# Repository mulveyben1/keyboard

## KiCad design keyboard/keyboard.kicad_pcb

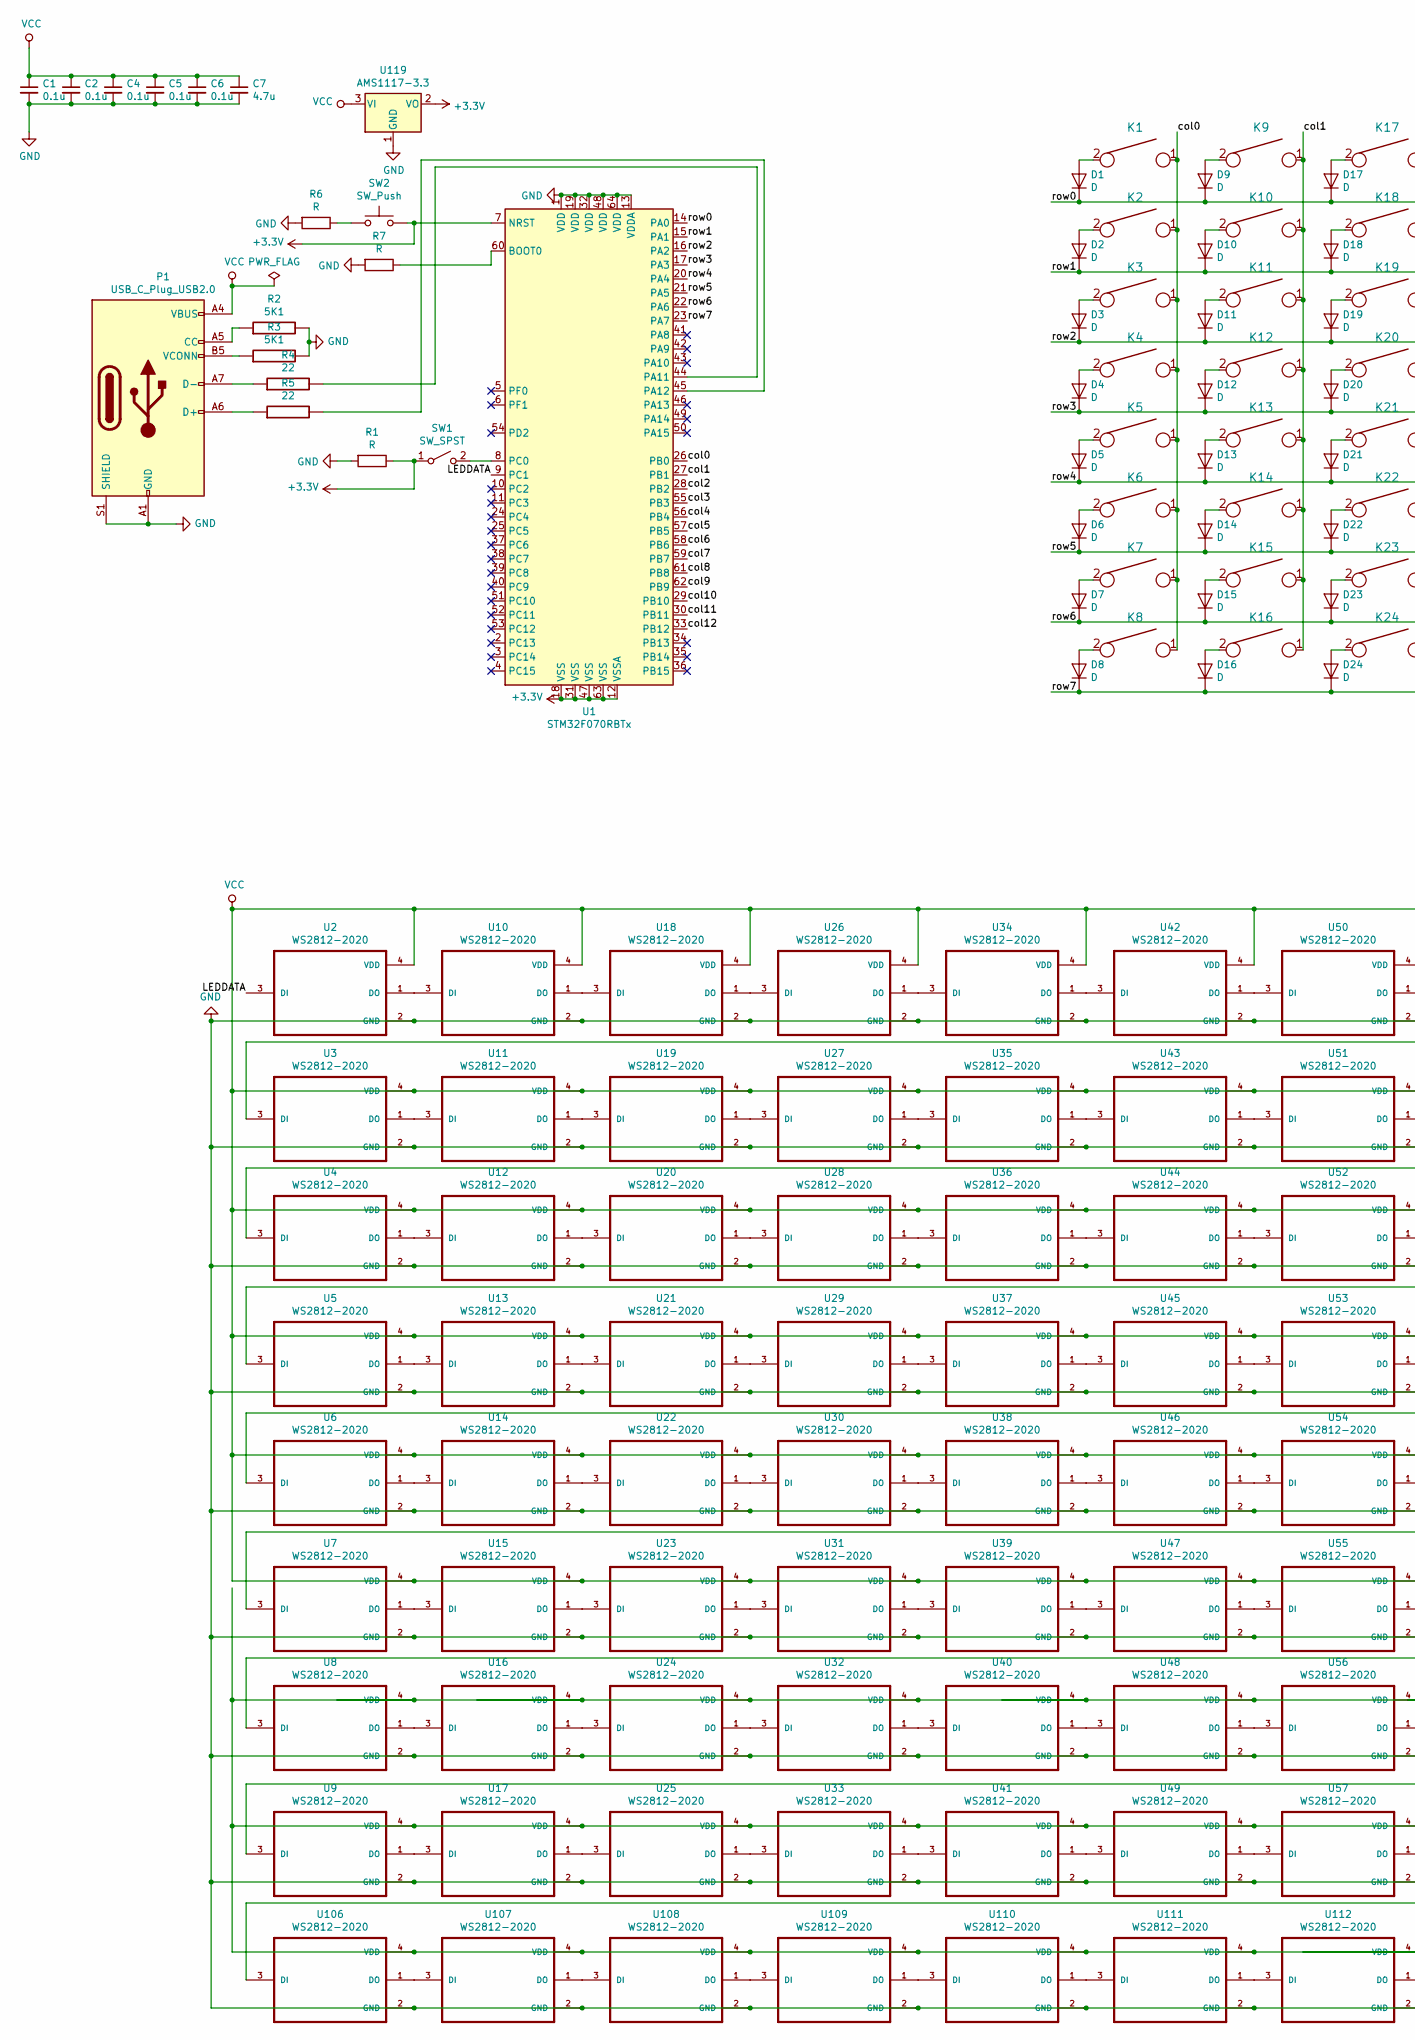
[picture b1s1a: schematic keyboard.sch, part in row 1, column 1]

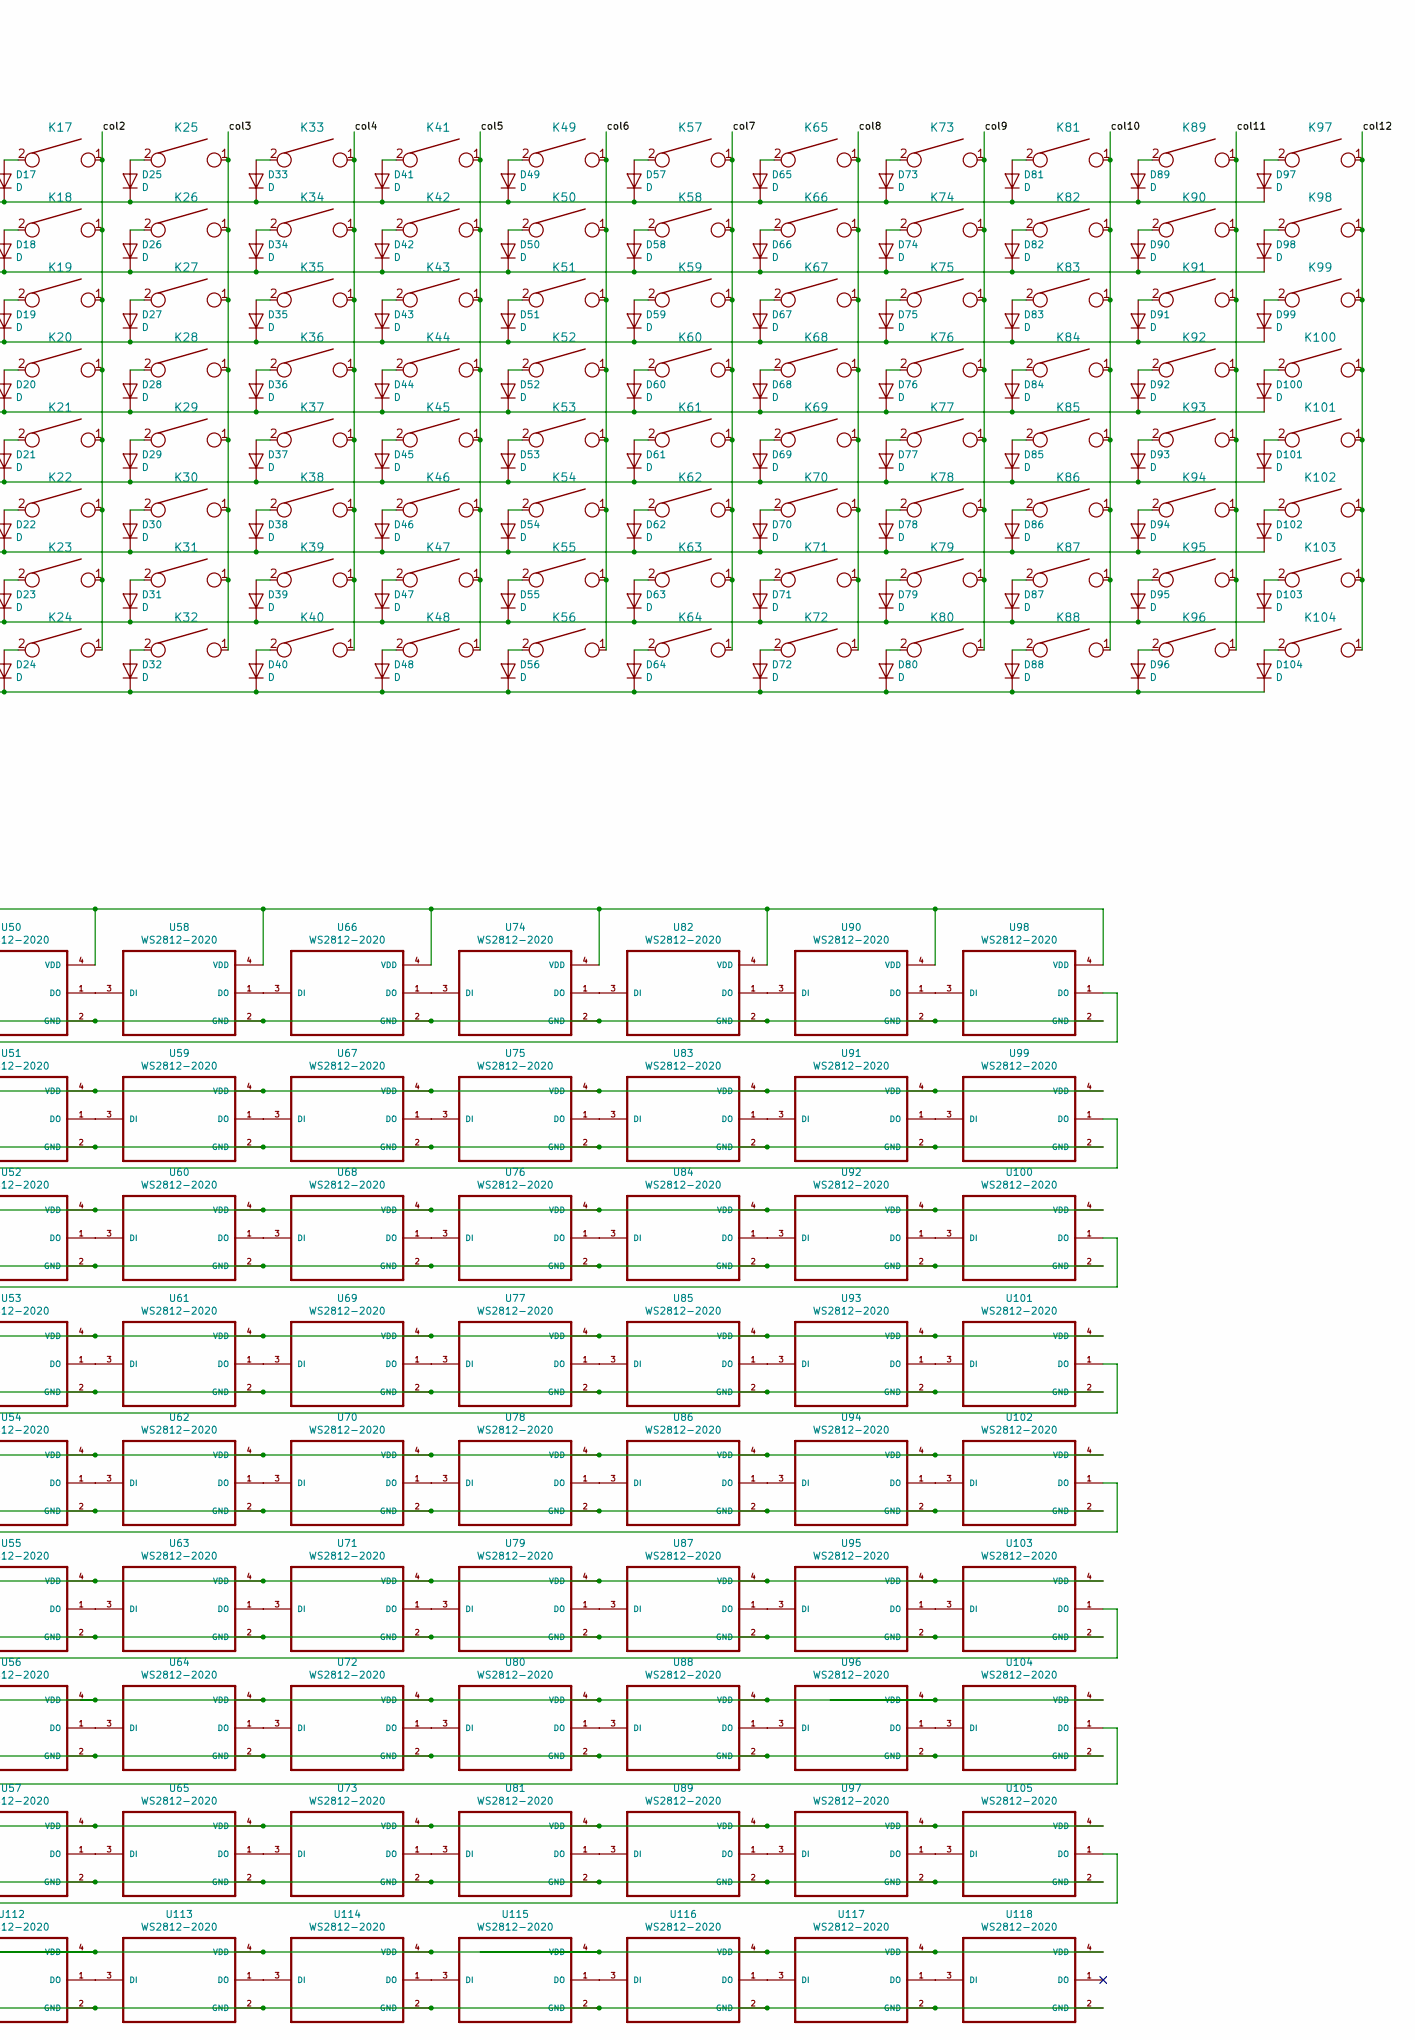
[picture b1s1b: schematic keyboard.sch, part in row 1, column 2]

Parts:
C1, C2, C4, C5, C6: 0.1u; C_0805_2012Metric
C7: 4.7u; C_0805_2012Metric
D1, D2, D3, D4, D5, D6, D7, D8, D9, D10, D11, D12, D13, D14, D15, D16, D17, D18, D19, D20, D21, D22, D23, D24, D25, D26, D27, D28, D29, D30, D31, D32, D33, D34, D35, D36, D37, D38, D39, D40, D41, D42, D43, D44, D45, D46, D47, D48, D49, D50, D51, D52, D53, D54, D55, D56, D57, D58, D59, D60, D61, D62, D63, D64, D65, D66, D67, D68, D69, D70, D71, D72, D73, D74, D75, D76, D77, D78, D79, D80, D81, D82, D83, D84, D85, D86, D87, D88, D89, D90, D91, D92, D93, D94, D95, D96, D97, D98, D99, D100, D101, D102, D103, D104: D; D_SOD123_axial
K1, K2, K3, K4, K5, K6, K7, K8, K9, K10, K11, K12, K13, K14, K15, K16, K17, K18, K19, K20, K21, K22, K23, K24, K25, K26, K27, K28, K29, K30, K31, K32, K33, K34, K35, K36, K37, K38, K39, K40, K41, K42, K43, K44, K45, K46, K47, K48, K49, K50, K51, K52, K53, K54, K55, K56, K57, K58, K59, K60, K61, K62, K63, K64, K65, K66, K67, K68, K69, K70, K71, K72, K73, K74, K75, K76, K77, K78, K79, K80, K81, K82, K83, K84, K85, K86, K87, K88, K89, K90, K91, K92, K93, K94, K95, K96, K97, K98, K99, K100, K101, K102, K103, K104: KEYSW; Mx_Alps_100
P1: USB_C_Plug_USB2.0; USB_C_Receptacle_Amphenol_12401548E4-2A
R1, R6, R7: R; C_0805_2012Metric
R2, R3: 5K1; R_0805_2012Metric
R4, R5: 22; R_0805_2012Metric
SW1: SW_SPST; SW_Slide_1P2T_CK_OS102011MS2Q
SW2: SW_Push; Push_E-Switch_KS01Q01
U1: STM32F070RBTx; LQFP-64_10x10mm_P0.5mm
U2, U3, U4, U5, U6, U7, U8, U9, U10, U11, U12, U13, U14, U15, U16, U17, U18, U19, U20, U21, U22, U23, U24, U25, U26, U27, U28, U29, U30, U31, U32, U33, U34, U35, U36, U37, U38, U39, U40, U41, U42, U43, U44, U45, U46, U47, U48, U49, U50, U51, U52, U53, U54, U55, U56, U57, U58, U59, U60, U61, U62, U63, U64, U65, U66, U67, U68, U69, U70, U71, U72, U73, U74, U75, U76, U77, U78, U79, U80, U81, U82, U83, U84, U85, U86, U87, U88, U89, U90, U91, U92, U93, U94, U95, U96, U97, U98, U99, U100, U101, U102, U103, U104, U105, U106, U107, U108, U109, U110, U111, U112, U113, U114, U115, U116, U117, U118: WS2812-2020; LED_WS2812-2020
U119: AMS1117-3.3; SOT-223-3_TabPin2

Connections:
+3V3: R1.1, SW1.1 (A), SW2.2, U1.7 (NRST), U1.12 (VSSA), U1.18 (VSS), U1.31 (VSS), U1.47 (VSS), U1.63 (VSS), U119.2 (VO)
/LEDDATA: U1.9 (PC1), U2.3 (DI)
/col0: K1.1, K2.1, K3.1, K4.1, K5.1, K6.1, K7.1, K8.1, U1.26 (PB0)
/col1: K9.1, K10.1, K11.1, K12.1, K13.1, K14.1, K15.1, K16.1, U1.27 (PB1)
/col2: K17.1, K18.1, K19.1, K20.1, K21.1, K22.1, K23.1, K24.1, U1.28 (PB2)
/col3: K25.1, K26.1, K27.1, K28.1, K29.1, K30.1, K31.1, K32.1, U1.55 (PB3)
/col4: K33.1, K34.1, K35.1, K36.1, K37.1, K38.1, K39.1, K40.1, U1.56 (PB4)
/col5: K41.1, K42.1, K43.1, K44.1, K45.1, K46.1, K47.1, K48.1, U1.57 (PB5)
/col6: K49.1, K50.1, K51.1, K52.1, K53.1, K54.1, K55.1, K56.1, U1.58 (PB6)
/col7: K57.1, K58.1, K59.1, K60.1, K61.1, K62.1, K63.1, K64.1, U1.59 (PB7)
/col8: K65.1, K66.1, K67.1, K68.1, K69.1, K70.1, K71.1, K72.1, U1.61 (PB8)
/col9: K73.1, K74.1, K75.1, K76.1, K77.1, K78.1, K79.1, K80.1, U1.62 (PB9)
/col10: K81.1, K82.1, K83.1, K84.1, K85.1, K86.1, K87.1, K88.1, U1.29 (PB10)
/col11: K89.1, K90.1, K91.1, K92.1, K93.1, K94.1, K95.1, K96.1, U1.30 (PB11)
/col12: K97.1, K98.1, K99.1, K100.1, K101.1, K102.1, K103.1, K104.1, U1.33 (PB12)
/row0: D1.1 (K), D9.1 (K), D17.1 (K), D25.1 (K), D33.1 (K), D41.1 (K), D49.1 (K), D57.1 (K), D65.1 (K), D73.1 (K), D81.1 (K), D89.1 (K), D97.1 (K), U1.14 (PA0)
/row1: D2.1 (K), D10.1 (K), D18.1 (K), D26.1 (K), D34.1 (K), D42.1 (K), D50.1 (K), D58.1 (K), D66.1 (K), D74.1 (K), D82.1 (K), D90.1 (K), D98.1 (K), U1.15 (PA1)
/row2: D3.1 (K), D11.1 (K), D19.1 (K), D27.1 (K), D35.1 (K), D43.1 (K), D51.1 (K), D59.1 (K), D67.1 (K), D75.1 (K), D83.1 (K), D91.1 (K), D99.1 (K), U1.16 (PA2)
/row3: D4.1 (K), D12.1 (K), D20.1 (K), D28.1 (K), D36.1 (K), D44.1 (K), D52.1 (K), D60.1 (K), D68.1 (K), D76.1 (K), D84.1 (K), D92.1 (K), D100.1 (K), U1.17 (PA3)
/row4: D5.1 (K), D13.1 (K), D21.1 (K), D29.1 (K), D37.1 (K), D45.1 (K), D53.1 (K), D61.1 (K), D69.1 (K), D77.1 (K), D85.1 (K), D93.1 (K), D101.1 (K), U1.20 (PA4)
/row5: D6.1 (K), D14.1 (K), D22.1 (K), D30.1 (K), D38.1 (K), D46.1 (K), D54.1 (K), D62.1 (K), D70.1 (K), D78.1 (K), D86.1 (K), D94.1 (K), D102.1 (K), U1.21 (PA5)
/row6: D7.1 (K), D15.1 (K), D23.1 (K), D31.1 (K), D39.1 (K), D47.1 (K), D55.1 (K), D63.1 (K), D71.1 (K), D79.1 (K), D87.1 (K), D95.1 (K), D103.1 (K), U1.22 (PA6)
/row7: D8.1 (K), D16.1 (K), D24.1 (K), D32.1 (K), D40.1 (K), D48.1 (K), D56.1 (K), D64.1 (K), D72.1 (K), D80.1 (K), D88.1 (K), D96.1 (K), D104.1 (K), U1.23 (PA7)
GND: C1.2, C2.2, C4.2, C5.2, C6.2, C7.2, P1.A1 (GND), P1.A12 (GND), P1.B1 (GND), P1.B12 (GND), P1.S1 (SHIELD), R1.2, R2.2, R3.2, R6.2, R7.2, U1.1 (VDD), U1.13 (VDDA), U1.19 (VDD), U1.32 (VDD), U1.48 (VDD), U1.64 (VDD), U2.2 (GND), U3.2 (GND), U4.2 (GND), U5.2 (GND), U6.2 (GND), U7.2 (GND), U8.2 (GND), U9.2 (GND), U10.2 (GND), U11.2 (GND), U12.2 (GND), U13.2 (GND), U14.2 (GND), U15.2 (GND), U16.2 (GND), U17.2 (GND), U18.2 (GND), U19.2 (GND), U20.2 (GND), U21.2 (GND), U22.2 (GND), U23.2 (GND), U24.2 (GND), U25.2 (GND), U26.2 (GND), U27.2 (GND), U28.2 (GND), U29.2 (GND), U30.2 (GND), U31.2 (GND), U32.2 (GND), U33.2 (GND), U34.2 (GND), U35.2 (GND), U36.2 (GND), U37.2 (GND), U38.2 (GND), U39.2 (GND), U40.2 (GND), U41.2 (GND), U42.2 (GND), U43.2 (GND), U44.2 (GND), U45.2 (GND), U46.2 (GND), U47.2 (GND), U48.2 (GND), U49.2 (GND), U50.2 (GND), U51.2 (GND), U52.2 (GND), U53.2 (GND), U54.2 (GND), U55.2 (GND), U56.2 (GND), U57.2 (GND), U58.2 (GND), U59.2 (GND), U60.2 (GND), U61.2 (GND), U62.2 (GND), U63.2 (GND), U64.2 (GND), U65.2 (GND), U66.2 (GND), U67.2 (GND), U68.2 (GND), U69.2 (GND), U70.2 (GND), U71.2 (GND), U72.2 (GND), U73.2 (GND), U74.2 (GND), U75.2 (GND), U76.2 (GND), U77.2 (GND), U78.2 (GND), U79.2 (GND), U80.2 (GND), U81.2 (GND), U82.2 (GND), U83.2 (GND), U84.2 (GND), U85.2 (GND), U86.2 (GND), U87.2 (GND), U88.2 (GND), U89.2 (GND), U90.2 (GND), U91.2 (GND), U92.2 (GND), U93.2 (GND), U94.2 (GND), U95.2 (GND), U96.2 (GND), U97.2 (GND), U98.2 (GND), U99.2 (GND), U100.2 (GND), U101.2 (GND), U102.2 (GND), U103.2 (GND), U104.2 (GND), U105.2 (GND), U106.2 (GND), U107.2 (GND), U108.2 (GND), U109.2 (GND), U110.2 (GND), U111.2 (GND), U112.2 (GND), U113.2 (GND), U114.2 (GND), U115.2 (GND), U116.2 (GND), U117.2 (GND), U118.2 (GND), U119.1 (GND)
unnamed: D1.2 (A), K1.2
unnamed: D2.2 (A), K2.2
unnamed: D3.2 (A), K3.2
unnamed: D4.2 (A), K4.2
unnamed: D5.2 (A), K5.2
unnamed: D6.2 (A), K6.2
unnamed: D7.2 (A), K7.2
unnamed: D8.2 (A), K8.2
unnamed: D9.2 (A), K9.2
unnamed: D10.2 (A), K10.2
unnamed: D11.2 (A), K11.2
unnamed: D12.2 (A), K12.2
unnamed: D13.2 (A), K13.2
unnamed: D14.2 (A), K14.2
unnamed: D15.2 (A), K15.2
unnamed: D16.2 (A), K16.2
unnamed: D17.2 (A), K17.2
unnamed: D18.2 (A), K18.2
unnamed: D19.2 (A), K19.2
unnamed: D20.2 (A), K20.2
unnamed: D21.2 (A), K21.2
unnamed: D22.2 (A), K22.2
unnamed: D23.2 (A), K23.2
unnamed: D24.2 (A), K24.2
unnamed: D25.2 (A), K25.2
unnamed: D26.2 (A), K26.2
unnamed: D27.2 (A), K27.2
unnamed: D28.2 (A), K28.2
unnamed: D29.2 (A), K29.2
unnamed: D30.2 (A), K30.2
unnamed: D31.2 (A), K31.2
unnamed: D32.2 (A), K32.2
unnamed: D33.2 (A), K33.2
unnamed: D34.2 (A), K34.2
unnamed: D35.2 (A), K35.2
unnamed: D36.2 (A), K36.2
unnamed: D37.2 (A), K37.2
unnamed: D38.2 (A), K38.2
unnamed: D39.2 (A), K39.2
unnamed: D40.2 (A), K40.2
unnamed: D41.2 (A), K41.2
unnamed: D42.2 (A), K42.2
unnamed: D43.2 (A), K43.2
unnamed: D44.2 (A), K44.2
unnamed: D45.2 (A), K45.2
unnamed: D46.2 (A), K46.2
unnamed: D47.2 (A), K47.2
unnamed: D48.2 (A), K48.2
unnamed: D49.2 (A), K49.2
unnamed: D50.2 (A), K50.2
unnamed: D51.2 (A), K51.2
unnamed: D52.2 (A), K52.2
unnamed: D53.2 (A), K53.2
unnamed: D54.2 (A), K54.2
unnamed: D55.2 (A), K55.2
unnamed: D56.2 (A), K56.2
unnamed: D57.2 (A), K57.2
unnamed: D58.2 (A), K58.2
unnamed: D59.2 (A), K59.2
unnamed: D60.2 (A), K60.2
unnamed: D61.2 (A), K61.2
unnamed: D62.2 (A), K62.2
unnamed: D63.2 (A), K63.2
unnamed: D64.2 (A), K64.2
unnamed: D65.2 (A), K65.2
unnamed: D66.2 (A), K66.2
unnamed: D67.2 (A), K67.2
unnamed: D68.2 (A), K68.2
unnamed: D69.2 (A), K69.2
unnamed: D70.2 (A), K70.2
unnamed: D71.2 (A), K71.2
unnamed: D72.2 (A), K72.2
unnamed: D73.2 (A), K73.2
unnamed: D74.2 (A), K74.2
unnamed: D75.2 (A), K75.2
unnamed: D76.2 (A), K76.2
unnamed: D77.2 (A), K77.2
unnamed: D78.2 (A), K78.2
unnamed: D79.2 (A), K79.2
unnamed: D80.2 (A), K80.2
unnamed: D81.2 (A), K81.2
unnamed: D82.2 (A), K82.2
unnamed: D83.2 (A), K83.2
unnamed: D84.2 (A), K84.2
unnamed: D85.2 (A), K85.2
unnamed: D86.2 (A), K86.2
unnamed: D87.2 (A), K87.2
unnamed: D88.2 (A), K88.2
unnamed: D89.2 (A), K89.2
unnamed: D90.2 (A), K90.2
unnamed: D91.2 (A), K91.2
unnamed: D92.2 (A), K92.2
unnamed: D93.2 (A), K93.2
unnamed: D94.2 (A), K94.2
unnamed: D95.2 (A), K95.2
unnamed: D96.2 (A), K96.2
unnamed: D97.2 (A), K97.2
unnamed: D98.2 (A), K98.2
unnamed: D99.2 (A), K99.2
unnamed: D100.2 (A), K100.2
unnamed: D101.2 (A), K101.2
unnamed: D102.2 (A), K102.2
unnamed: D103.2 (A), K103.2
unnamed: D104.2 (A), K104.2
unnamed: P1.A5 (CC), R2.1
unnamed: P1.A6 (D+), R5.1
unnamed: P1.A7 (D-), R4.1
unnamed: P1.B5 (VCONN), R3.1
unnamed: R4.2, U1.44 (PA11)
unnamed: R5.2, U1.45 (PA12)
unnamed: R6.1, SW2.1
unnamed: R7.1, U1.60 (BOOT0)
unnamed: SW1.2 (B), U1.8 (PC0)
unnamed: U3.3 (DI), U98.1 (DO)
unnamed: U4.3 (DI), U99.1 (DO)
unnamed: U10.1 (DO), U18.3 (DI)
unnamed: U2.1 (DO), U10.3 (DI)
unnamed: U11.1 (DO), U19.3 (DI)
unnamed: U3.1 (DO), U11.3 (DI)
unnamed: U12.1 (DO), U20.3 (DI)
unnamed: U4.1 (DO), U12.3 (DI)
unnamed: U13.1 (DO), U21.3 (DI)
unnamed: U5.1 (DO), U13.3 (DI)
unnamed: U14.1 (DO), U22.3 (DI)
unnamed: U6.1 (DO), U14.3 (DI)
unnamed: U15.1 (DO), U23.3 (DI)
unnamed: U7.1 (DO), U15.3 (DI)
unnamed: U16.1 (DO), U24.3 (DI)
unnamed: U8.1 (DO), U16.3 (DI)
unnamed: U17.1 (DO), U25.3 (DI)
unnamed: U9.1 (DO), U17.3 (DI)
unnamed: U18.1 (DO), U26.3 (DI)
unnamed: U19.1 (DO), U27.3 (DI)
unnamed: U20.1 (DO), U28.3 (DI)
unnamed: U21.1 (DO), U29.3 (DI)
unnamed: U22.1 (DO), U30.3 (DI)
unnamed: U23.1 (DO), U31.3 (DI)
unnamed: U24.1 (DO), U32.3 (DI)
unnamed: U25.1 (DO), U33.3 (DI)
unnamed: U26.1 (DO), U34.3 (DI)
unnamed: U27.1 (DO), U35.3 (DI)
unnamed: U28.1 (DO), U36.3 (DI)
unnamed: U29.1 (DO), U37.3 (DI)
unnamed: U30.1 (DO), U38.3 (DI)
unnamed: U31.1 (DO), U39.3 (DI)
unnamed: U32.1 (DO), U40.3 (DI)
unnamed: U33.1 (DO), U41.3 (DI)
unnamed: U34.1 (DO), U42.3 (DI)
unnamed: U35.1 (DO), U43.3 (DI)
unnamed: U36.1 (DO), U44.3 (DI)
unnamed: U37.1 (DO), U45.3 (DI)
unnamed: U38.1 (DO), U46.3 (DI)
unnamed: U39.1 (DO), U47.3 (DI)
unnamed: U40.1 (DO), U48.3 (DI)
unnamed: U41.1 (DO), U49.3 (DI)
unnamed: U42.1 (DO), U50.3 (DI)
unnamed: U43.1 (DO), U51.3 (DI)
unnamed: U44.1 (DO), U52.3 (DI)
unnamed: U45.1 (DO), U53.3 (DI)
unnamed: U46.1 (DO), U54.3 (DI)
unnamed: U47.1 (DO), U55.3 (DI)
unnamed: U48.1 (DO), U56.3 (DI)
unnamed: U49.1 (DO), U57.3 (DI)
unnamed: U50.1 (DO), U58.3 (DI)
unnamed: U51.1 (DO), U59.3 (DI)
unnamed: U52.1 (DO), U60.3 (DI)
unnamed: U53.1 (DO), U61.3 (DI)
unnamed: U54.1 (DO), U62.3 (DI)
unnamed: U55.1 (DO), U63.3 (DI)
unnamed: U56.1 (DO), U64.3 (DI)
unnamed: U57.1 (DO), U65.3 (DI)
unnamed: U58.1 (DO), U66.3 (DI)
unnamed: U59.1 (DO), U67.3 (DI)
unnamed: U60.1 (DO), U68.3 (DI)
unnamed: U61.1 (DO), U69.3 (DI)
unnamed: U62.1 (DO), U70.3 (DI)
unnamed: U63.1 (DO), U71.3 (DI)
unnamed: U64.1 (DO), U72.3 (DI)
unnamed: U65.1 (DO), U73.3 (DI)
unnamed: U66.1 (DO), U74.3 (DI)
unnamed: U67.1 (DO), U75.3 (DI)
unnamed: U68.1 (DO), U76.3 (DI)
unnamed: U69.1 (DO), U77.3 (DI)
unnamed: U70.1 (DO), U78.3 (DI)
unnamed: U71.1 (DO), U79.3 (DI)
unnamed: U72.1 (DO), U80.3 (DI)
unnamed: U73.1 (DO), U81.3 (DI)
unnamed: U74.1 (DO), U82.3 (DI)
unnamed: U75.1 (DO), U83.3 (DI)
unnamed: U76.1 (DO), U84.3 (DI)
unnamed: U77.1 (DO), U85.3 (DI)
unnamed: U78.1 (DO), U86.3 (DI)
unnamed: U79.1 (DO), U87.3 (DI)
unnamed: U80.1 (DO), U88.3 (DI)
unnamed: U81.1 (DO), U89.3 (DI)
unnamed: U82.1 (DO), U90.3 (DI)
unnamed: U83.1 (DO), U91.3 (DI)
unnamed: U84.1 (DO), U92.3 (DI)
unnamed: U85.1 (DO), U93.3 (DI)
unnamed: U86.1 (DO), U94.3 (DI)
unnamed: U87.1 (DO), U95.3 (DI)
unnamed: U88.1 (DO), U96.3 (DI)
unnamed: U89.1 (DO), U97.3 (DI)
unnamed: U90.1 (DO), U98.3 (DI)
unnamed: U91.1 (DO), U99.3 (DI)
unnamed: U5.3 (DI), U100.1 (DO)
unnamed: U92.1 (DO), U100.3 (DI)
unnamed: U6.3 (DI), U101.1 (DO)
unnamed: U93.1 (DO), U101.3 (DI)
unnamed: U7.3 (DI), U102.1 (DO)
unnamed: U94.1 (DO), U102.3 (DI)
unnamed: U8.3 (DI), U103.1 (DO)
unnamed: U95.1 (DO), U103.3 (DI)
unnamed: U9.3 (DI), U104.1 (DO)
unnamed: U96.1 (DO), U104.3 (DI)
unnamed: U8.4 (VDD), U9.4 (VDD), U16.4 (VDD), U17.4 (VDD), U24.4 (VDD), U25.4 (VDD), U32.4 (VDD), U33.4 (VDD), U40.4 (VDD), U41.4 (VDD), U48.4 (VDD), U49.4 (VDD), U56.4 (VDD), U57.4 (VDD), U64.4 (VDD), U65.4 (VDD), U72.4 (VDD), U73.4 (VDD), U80.4 (VDD), U81.4 (VDD), U88.4 (VDD), U89.4 (VDD), U96.4 (VDD), U97.4 (VDD), U104.4 (VDD), U105.4 (VDD), U106.4 (VDD), U107.4 (VDD), U108.4 (VDD), U109.4 (VDD), U110.4 (VDD), U111.4 (VDD), U112.4 (VDD), U113.4 (VDD), U114.4 (VDD), U115.4 (VDD), U116.4 (VDD), U117.4 (VDD), U118.4 (VDD)
unnamed: U105.1 (DO), U106.3 (DI)
unnamed: U97.1 (DO), U105.3 (DI)
unnamed: U106.1 (DO), U107.3 (DI)
unnamed: U107.1 (DO), U108.3 (DI)
unnamed: U108.1 (DO), U109.3 (DI)
unnamed: U109.1 (DO), U110.3 (DI)
unnamed: U110.1 (DO), U111.3 (DI)
unnamed: U111.1 (DO), U112.3 (DI)
unnamed: U112.1 (DO), U113.3 (DI)
unnamed: U113.1 (DO), U114.3 (DI)
unnamed: U114.1 (DO), U115.3 (DI)
unnamed: U115.1 (DO), U116.3 (DI)
unnamed: U116.1 (DO), U117.3 (DI)
unnamed: U117.1 (DO), U118.3 (DI)
VCC: C1.1, C2.1, C4.1, C5.1, C6.1, C7.1, P1.A4 (VBUS), P1.A9 (VBUS), P1.B4 (VBUS), P1.B9 (VBUS), U2.4 (VDD), U3.4 (VDD), U4.4 (VDD), U5.4 (VDD), U6.4 (VDD), U7.4 (VDD), U10.4 (VDD), U11.4 (VDD), U12.4 (VDD), U13.4 (VDD), U14.4 (VDD), U15.4 (VDD), U18.4 (VDD), U19.4 (VDD), U20.4 (VDD), U21.4 (VDD), U22.4 (VDD), U23.4 (VDD), U26.4 (VDD), U27.4 (VDD), U28.4 (VDD), U29.4 (VDD), U30.4 (VDD), U31.4 (VDD), U34.4 (VDD), U35.4 (VDD), U36.4 (VDD), U37.4 (VDD), U38.4 (VDD), U39.4 (VDD), U42.4 (VDD), U43.4 (VDD), U44.4 (VDD), U45.4 (VDD), U46.4 (VDD), U47.4 (VDD), U50.4 (VDD), U51.4 (VDD), U52.4 (VDD), U53.4 (VDD), U54.4 (VDD), U55.4 (VDD), U58.4 (VDD), U59.4 (VDD), U60.4 (VDD), U61.4 (VDD), U62.4 (VDD), U63.4 (VDD), U66.4 (VDD), U67.4 (VDD), U68.4 (VDD), U69.4 (VDD), U70.4 (VDD), U71.4 (VDD), U74.4 (VDD), U75.4 (VDD), U76.4 (VDD), U77.4 (VDD), U78.4 (VDD), U79.4 (VDD), U82.4 (VDD), U83.4 (VDD), U84.4 (VDD), U85.4 (VDD), U86.4 (VDD), U87.4 (VDD), U90.4 (VDD), U91.4 (VDD), U92.4 (VDD), U93.4 (VDD), U94.4 (VDD), U95.4 (VDD), U98.4 (VDD), U99.4 (VDD), U100.4 (VDD), U101.4 (VDD), U102.4 (VDD), U103.4 (VDD), U119.3 (VI)

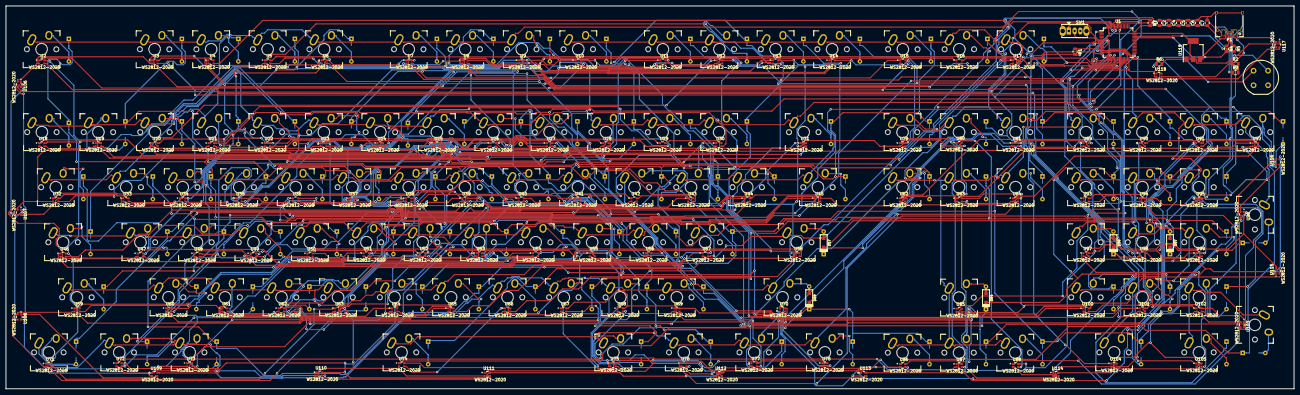
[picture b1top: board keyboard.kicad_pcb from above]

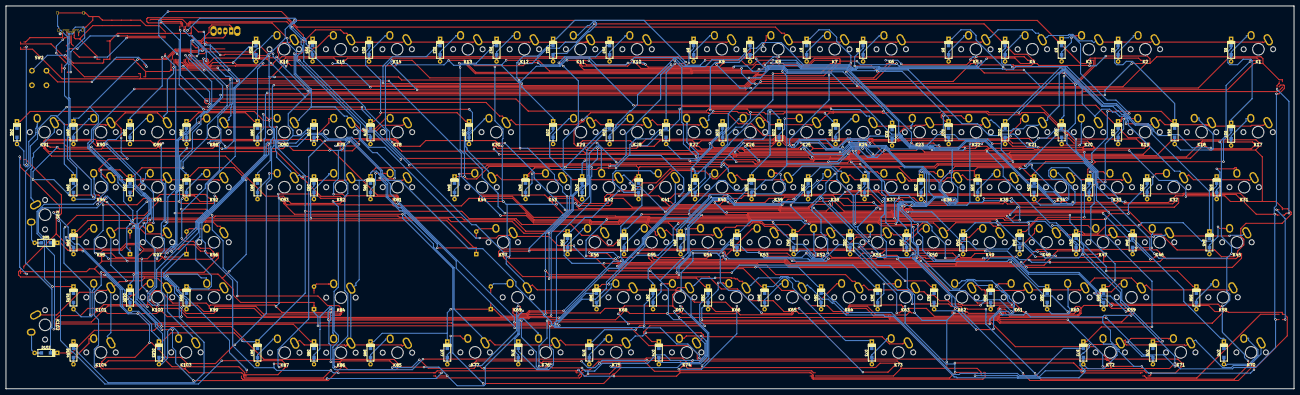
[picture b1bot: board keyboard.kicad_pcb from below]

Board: 2 copper layers, 444.5 x 132.1 mm, 343 parts (99 on the bottom side), 255 nets.

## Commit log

2019-09-06 beginnings of circuit & libraries
2019-09-07 add switches/leds
2019-09-08 arrange switches/diodes/other
2019-10-07 add datasheets
2019-11-01 finally figure out leds & remove led drivers
2019-11-10 routed with all leds + gerbers
